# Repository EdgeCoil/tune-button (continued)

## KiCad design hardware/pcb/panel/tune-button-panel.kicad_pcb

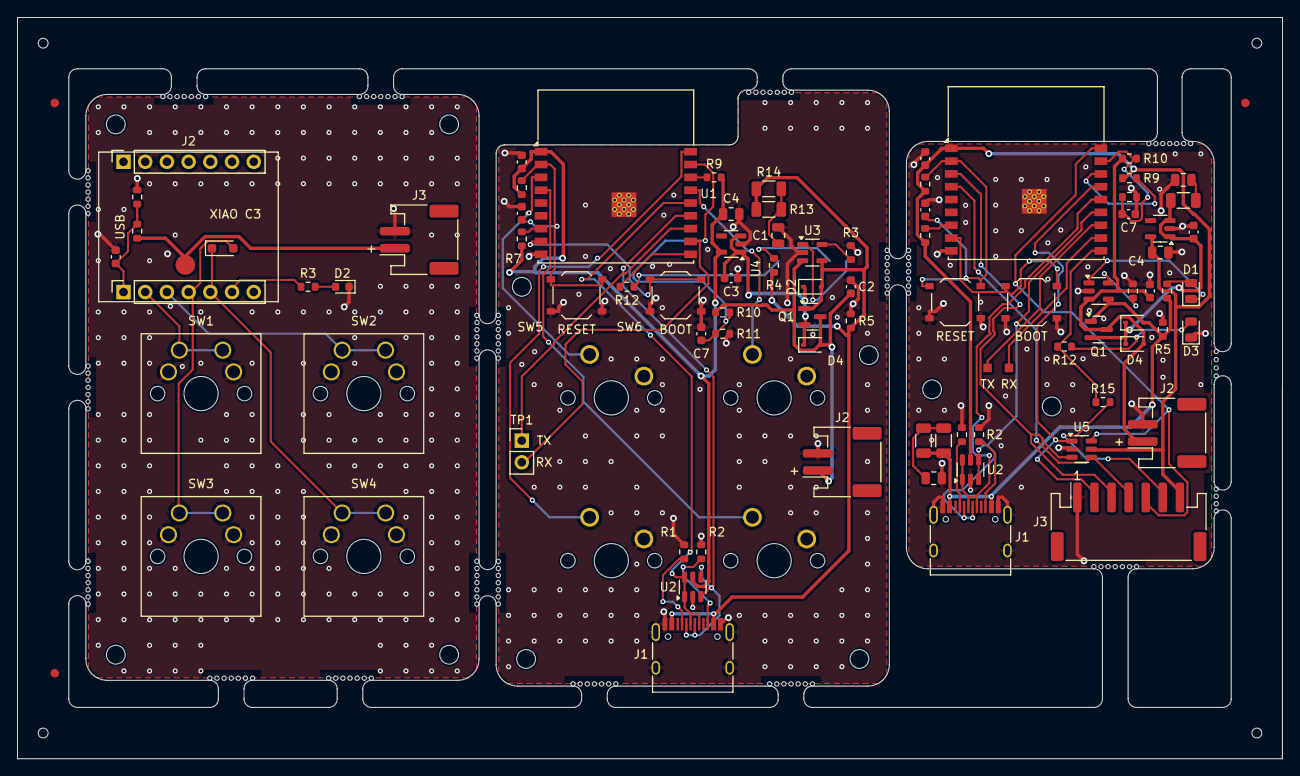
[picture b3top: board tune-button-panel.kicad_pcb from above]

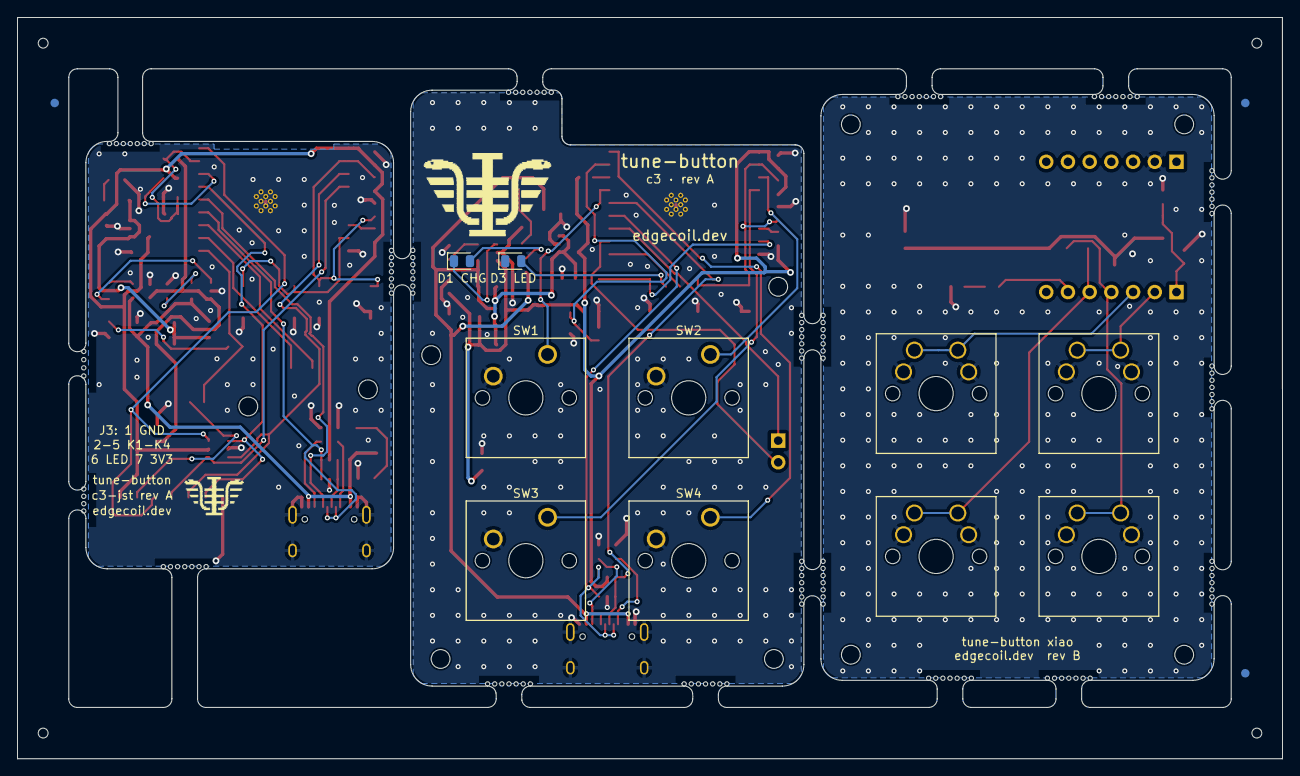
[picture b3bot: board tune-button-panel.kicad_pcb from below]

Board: 2 copper layers, 148.0 x 86.7 mm, 246 parts (9 on the bottom side), 63 nets.

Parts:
C1, C5, C5#2, C7, C7#2: 100n; C_0603_1608Metric
C1#2, C1#3, C8: 10u; C_0805_2012Metric
C2, C2#2: 4.7u; C_0603_1608Metric
C3, C3#2, C6, C6#2: 1u; C_0603_1608Metric
C4, C4#2: 22u; C_0805_2012Metric
D1: 1N4148WS; D_SOD-323_HandSoldering
D1#2, D1#3: CHG red; LED_0805_2012Metric
D2, D2#2, D4, D4#2: 1N5819WS; D_SOD-323
D2#3: LED; LED_0603_1608Metric
D3, D3#2: LED; LED_0805_2012Metric
H1, H1#2, H1#3, H2, H2#2, H2#3, H3, H3#2, H4, H4#2: M2; MountingHole_2.2mm_M2
J1: XIAO D0-D6; PinSocket_1x07_P2.54mm_Vertical
J1#2, J1#3: USB-C; USB_C_Receptacle_HRO_TYPE-C-31-M-12
J2, J2#2, J3: LiPo; JST_PH_S2B-PH-SM4-TB_1x02-1MP_P2.00mm_Horizontal
J2#3: XIAO 5V-D7; PinSocket_1x07_P2.54mm_Vertical
J3#2: Buttons; JST_PH_S7B-PH-SM4-TB_1x07-1MP_P2.00mm_Horizontal
J4: pogo VBAT; PogoPin_YTC1P_D2.0_SMD
KiKit_FID_B_1, KiKit_FID_B_2, KiKit_FID_B_3: Fiducial
KiKit_FID_T_1, KiKit_FID_T_2, KiKit_FID_T_3: Fiducial
KiKit_MB_1_1, KiKit_MB_1_2, KiKit_MB_1_3, KiKit_MB_1_4, KiKit_MB_1_5, KiKit_MB_1_6, KiKit_MB_1_7, KiKit_MB_2_1, KiKit_MB_2_2, KiKit_MB_2_3, KiKit_MB_2_4, KiKit_MB_2_5, KiKit_MB_2_6, KiKit_MB_2_7, KiKit_MB_3_1, KiKit_MB_3_2, KiKit_MB_3_3, KiKit_MB_3_4, KiKit_MB_3_5, KiKit_MB_3_6, KiKit_MB_3_7, KiKit_MB_4_1, KiKit_MB_4_2, KiKit_MB_4_3, KiKit_MB_4_4, KiKit_MB_4_5, KiKit_MB_4_6, KiKit_MB_4_7, KiKit_MB_5_1, KiKit_MB_5_2, KiKit_MB_5_3, KiKit_MB_5_4, KiKit_MB_5_5, KiKit_MB_5_6, KiKit_MB_5_7, KiKit_MB_6_1, KiKit_MB_6_2, KiKit_MB_6_3, KiKit_MB_6_4, KiKit_MB_6_5, KiKit_MB_6_6, KiKit_MB_6_7, KiKit_MB_7_1, KiKit_MB_7_2, KiKit_MB_7_3, KiKit_MB_7_4, KiKit_MB_7_5, KiKit_MB_7_6, KiKit_MB_7_7, KiKit_MB_8_1, KiKit_MB_8_2, KiKit_MB_8_3, KiKit_MB_8_4, KiKit_MB_8_5, KiKit_MB_8_6, KiKit_MB_8_7, KiKit_MB_9_1, KiKit_MB_9_2, KiKit_MB_9_3, KiKit_MB_9_4, KiKit_MB_9_5, KiKit_MB_9_6, KiKit_MB_9_7, KiKit_MB_10_1, KiKit_MB_10_2, KiKit_MB_10_3, KiKit_MB_10_4, KiKit_MB_10_5, KiKit_MB_10_6, KiKit_MB_10_7, KiKit_MB_11_1, KiKit_MB_11_2, KiKit_MB_11_3, KiKit_MB_11_4, KiKit_MB_11_5, KiKit_MB_11_6, KiKit_MB_11_7, KiKit_MB_12_1, KiKit_MB_12_2, KiKit_MB_12_3, KiKit_MB_12_4, KiKit_MB_12_5, KiKit_MB_12_6, KiKit_MB_12_7, KiKit_MB_13_1, KiKit_MB_13_2, KiKit_MB_13_3, KiKit_MB_13_4, KiKit_MB_13_5, KiKit_MB_13_6, KiKit_MB_13_7, KiKit_MB_14_1, KiKit_MB_14_2, KiKit_MB_14_3, KiKit_MB_14_4, KiKit_MB_14_5, KiKit_MB_14_6, KiKit_MB_14_7, KiKit_MB_15_1, KiKit_MB_15_2, KiKit_MB_15_3, KiKit_MB_15_4, KiKit_MB_15_5, KiKit_MB_15_6, KiKit_MB_15_7, KiKit_MB_16_1, KiKit_MB_16_2, KiKit_MB_16_3, KiKit_MB_16_4, KiKit_MB_16_5, KiKit_MB_16_6, KiKit_MB_16_7, KiKit_MB_17_1, KiKit_MB_17_2, KiKit_MB_17_3, KiKit_MB_17_4, KiKit_MB_17_5, KiKit_MB_17_6, KiKit_MB_17_7, KiKit_MB_18_1, KiKit_MB_18_2, KiKit_MB_18_3, KiKit_MB_18_4, KiKit_MB_18_5, KiKit_MB_18_6, KiKit_MB_18_7, KiKit_MB_19_2, KiKit_MB_19_3, KiKit_MB_19_4, KiKit_MB_19_5, KiKit_MB_20_2, KiKit_MB_20_3, KiKit_MB_20_4, KiKit_MB_20_5: NPTH
KiKit_TO_1, KiKit_TO_2, KiKit_TO_3, KiKit_TO_4: NPTH
Q1, Q1#2: AO3401A; SOT-23
R1, R1#2, R2#2, R2#3: 5.1k; R_0603_1608Metric
R1#3, R2, R10, R10#2, R11, R11#2: 220k; R_0603_1608Metric
R3, R4, R4#2, R12, R12#2: 1k; R_0603_1608Metric
R3#2, R3#3: 4.7k; R_0603_1608Metric
R5, R5#2: 3.3k; R_0603_1608Metric
R6, R6#2, R7, R7#2, R9, R9#2: 10k; R_0603_1608Metric
R13, R13#2, R14, R14#2, R16: 1; R_1206_3216Metric
R15: 330; R_0603_1608Metric
SW1, SW2, SW3, SW4: MX switch; SW_Cherry_MX_1.00u_PCB_Reversible
SW1#2, SW2#2, SW3#2, SW4#2: MX switch; SW_Cherry_MX_1.00u_PCB
SW5, SW5#2: RESET; SW_Push_1P1T_XKB_TS-1187A
SW6, SW6#2: BOOT; SW_Push_1P1T_XKB_TS-1187A
TP1: UART; PinHeader_1x02_P2.54mm_Vertical
TP1#2: TXD; TestPoint_Pad_1.0x1.0mm
TP2: RXD; TestPoint_Pad_1.0x1.0mm
U1, U1#2: ESP32-C3-WROOM-02-N4; ESP32-C3-WROOM-02
U2, U2#2, U5: SRV05-4; SOT-23-6
U3, U3#2: TP4054; SOT-23-5
U4, U4#2: RT9080-3.3; SOT-23-5

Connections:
Board_0-GND: C1.2, D2#3.1, J2#3.2, J3.2, R2.2, SW1.2, SW2.2, SW3.2, SW4.2
Board_0-K1: J1.2, SW1.1
Board_0-K2: J1.3, SW2.1
Board_0-K3: D1.2, J1.4, SW3.1
Board_0-K4: D1.1, J1.5, SW4.1
Board_0-LED: J1.6, R3.1
Board_0-LED_A: D2#3.2, R3.2
Board_0-VBAT: J3.1, J4.1, R1#3.1
Board_0-VBAT_SENSE: C1.1, J1.1, R1#3.2, R2.1
Board_1-3V3: C4#2.1, C5#2.1, R6.1, R7.1, R9#2.1, U1.1, U2#2.5, U4#2.5
Board_1-CC1: J1#2.A5, R1.1
Board_1-CC2: J1#2.B5, R2#3.1
Board_1-CHG_A: D1#3.2, R4.2
Board_1-EN: C6.1, R6.2, SW5.1, U1.2
Board_1-GND: C1#2.2, C2#2.2, C3#2.2, C4#2.2, C5#2.2, C6.2, C7#2.2, D3#2.1, J1#2.A1, J1#2.A12, J1#2.B1, J1#2.B12, J1#2.S1, J2#2.2, R1.2, R2#3.2, R3#3.2, R5#2.2, R11#2.2, SW1#2.2, SW2#2.2, SW3#2.2, SW4#2.2, SW5.2, SW6.2, U1.9, U1.19, U2#2.2, U3#2.2, U4#2.2
Board_1-IO2: R9#2.2, U1.16
Board_1-IO8: R7.2, U1.7
Board_1-IO9: SW6.1, U1.8
Board_1-K1: SW1#2.1, U1.15
Board_1-K2: SW2#2.1, U1.3
Board_1-K3: SW3#2.1, U1.4
Board_1-K4: SW4#2.1, U1.18
Board_1-LED: R12.1, U1.10
Board_1-LED_A: D3#2.2, R12.2
Board_1-PROG: R3#3.1, U3#2.5
Board_1-RXD: TP1.2, U1.11
Board_1-STAT: D1#3.1, U3#2.1
Board_1-TXD: TP1.1, U1.12
Board_1-USB_DN: J1#2.A7, J1#2.B7, U1.13, U2#2.3, U2#2.4
Board_1-USB_DP: J1#2.A6, J1#2.B6, U1.14, U2#2.1, U2#2.6
Board_1-VBAT: C2#2.1, D4.2, J2#2.1, Q1#2.3, R10#2.1, U3#2.3
Board_1-VBAT_SENSE: C7#2.1, R10#2.2, R11#2.1, U1.17
Board_1-VBUS: D2#2.2, J1#2.A4, J1#2.A9, J1#2.B4, J1#2.B9, Q1#2.1, R4.1, R5#2.1, R13#2.1, R14#2.1, U3#2.4
Board_1-VBUS_C: C1#2.1, R13#2.2, R14#2.2
Board_1-VSYS: C3#2.1, D2#2.1, D4.1, Q1#2.2, U4#2.1, U4#2.3
Board_2-3V3: C4.1, C5.1, J3#2.7, R6#2.1, R7#2.1, R9.1, U1#2.1, U2.5, U4.5, U5.5
Board_2-CC1: J1#3.A5, R1#2.1
Board_2-CC2: J1#3.B5, R2#2.1
Board_2-CHG_A: D1#2.2, R4#2.2
Board_2-EN: C6#2.1, R6#2.2, SW5#2.1, U1#2.2
Board_2-GND: C1#3.2, C2.2, C3.2, C4.2, C5.2, C6#2.2, C7.2, C8.2, D3.1, J1#3.A1, J1#3.A12, J1#3.B1, J1#3.B12, J1#3.S1, J2.2, J3#2.1, R1#2.2, R2#2.2, R3#2.2, R5.2, R11.2, SW5#2.2, SW6#2.2, U1#2.9, U1#2.19, U2.2, U3.2, U4.2, U5.2
Board_2-IO2: R9.2, U1#2.16
Board_2-IO8: R7#2.2, U1#2.7
Board_2-IO9: SW6#2.1, U1#2.8
Board_2-K1: J3#2.2, U1#2.15, U5.1
Board_2-K2: J3#2.3, U1#2.3, U5.3
Board_2-K3: J3#2.4, U1#2.4, U5.4
Board_2-K4: J3#2.5, U1#2.18, U5.6
Board_2-LED: R12#2.1, R15.1, U1#2.10
Board_2-LED_A: D3.2, R12#2.2
Board_2-LED_OUT: J3#2.6, R15.2
Board_2-PROG: R3#2.1, U3.5
Board_2-RXD: TP2.1, U1#2.11
Board_2-STAT: D1#2.1, U3.1
Board_2-TXD: TP1#2.1, U1#2.12
Board_2-USB_DN: J1#3.A7, J1#3.B7, U1#2.13, U2.3, U2.4
Board_2-USB_DP: J1#3.A6, J1#3.B6, U1#2.14, U2.1, U2.6
Board_2-VBAT: C2.1, D4#2.2, J2.1, Q1.3, R10.1, U3.3
Board_2-VBAT_SENSE: C7.1, R10.2, R11.1, U1#2.17
Board_2-VBUS: D2.2, J1#3.A4, J1#3.A9, J1#3.B4, J1#3.B9, Q1.1, R4#2.1, R5.1, R13.1, R14.1, U3.4
Board_2-VBUS_C: C1#3.1, R13.2, R14.2
Board_2-VSYS: C3.1, D2.1, D4#2.1, Q1.2, R16.1, U4.1, U4.3
Board_2-VSYS_D: C8.1, R16.2
